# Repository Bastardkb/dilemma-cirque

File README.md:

Work in progress.

Cirque trackpad module for the dilemma keyboard

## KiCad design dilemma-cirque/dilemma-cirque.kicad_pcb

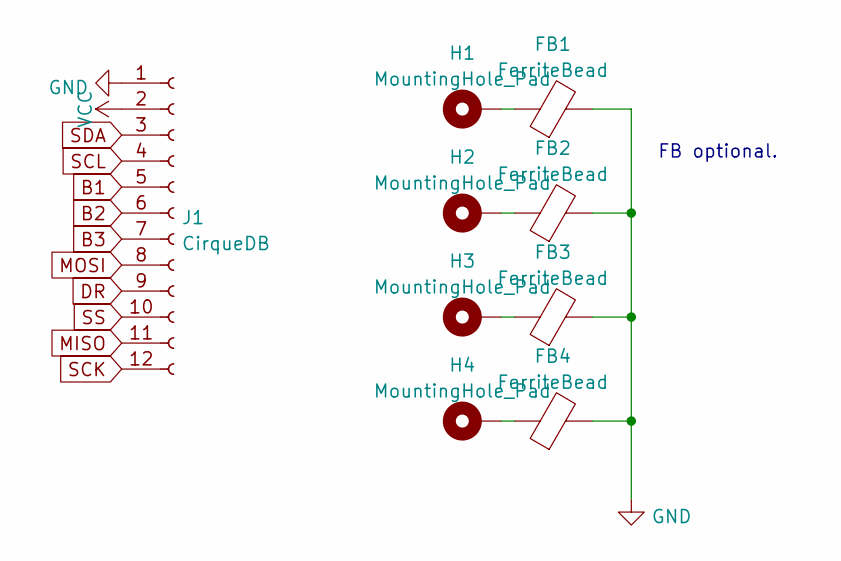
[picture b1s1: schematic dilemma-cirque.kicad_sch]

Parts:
FB1, FB2, FB3, FB4: FerriteBead; L_0805_2012Metric_Pad1.15x1.40mm_HandSolder
H1, H2, H3, H4: MountingHole_Pad; MountingHole_3mm_Pad
J1: CirqueDB; CirqueDB_compact-BK

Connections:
B1: J1.5
B2: J1.6
B3: J1.7
DR: J1.9
GND: FB1.2, FB2.2, FB3.2, FB4.2, J1.1
MISO: J1.11
MOSI: J1.8
unnamed: FB1.1, H1.1
unnamed: FB2.1, H2.1
unnamed: FB3.1, H3.1
unnamed: FB4.1, H4.1
SCK: J1.12
SCL: J1.4
SDA: J1.3
SS: J1.10
VCC: J1.2

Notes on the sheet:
FB optional.

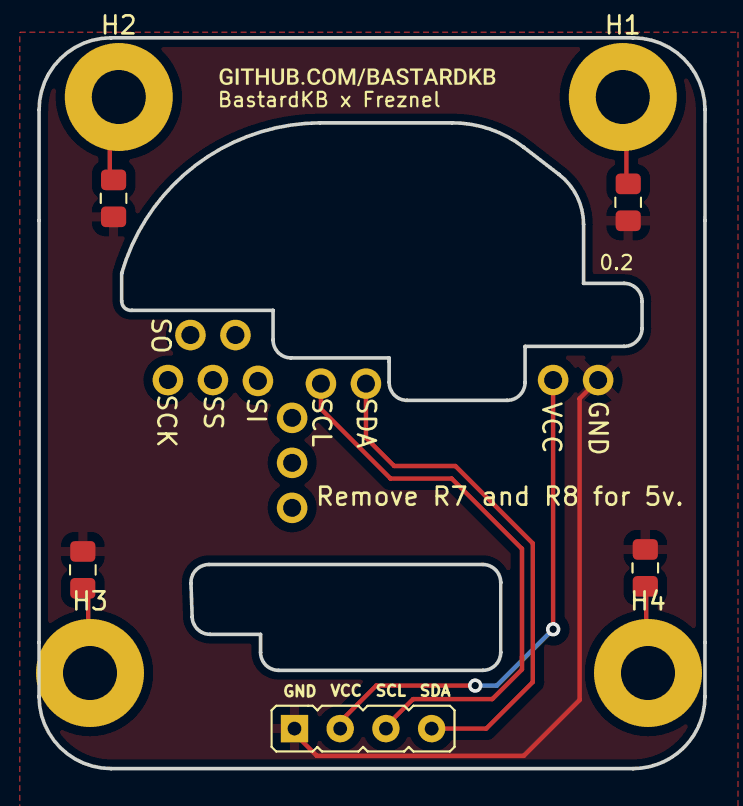
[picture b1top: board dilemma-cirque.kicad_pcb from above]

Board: 2 copper layers, 37.0 x 40.6 mm, 11 parts (1 on the bottom side), 5 nets.

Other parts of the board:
kibuzzard-61F01A92, kibuzzard-61F01A92#2: G***; kibuzzard-61F01A92

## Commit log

2022-05-25 upload files
2022-05-26 clean up footprints
2022-05-26 zones
2022-05-26 Footprint library created, CirqueDB more compact
2022-05-27 silkscreen
2022-06-16 M2 to M3
